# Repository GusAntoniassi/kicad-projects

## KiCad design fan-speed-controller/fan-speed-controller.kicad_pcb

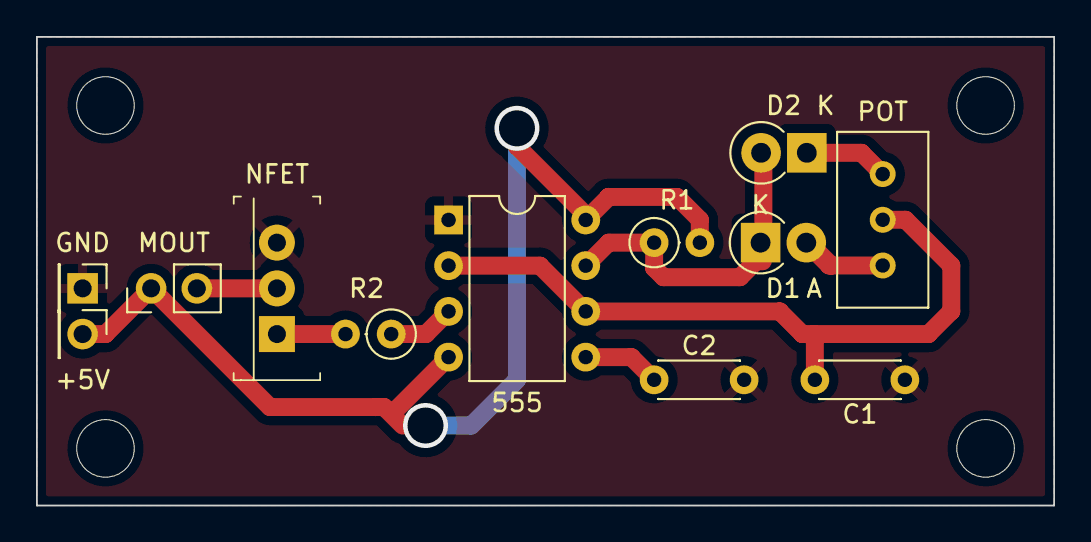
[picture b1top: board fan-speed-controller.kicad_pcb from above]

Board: 2 copper layers, 56.5 x 26.0 mm, 12 parts (0 on the bottom side), 10 nets.

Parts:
555: LM555xN; DIP-8_W7.62mm
+5V: MountingHole_Pad; PinHeader_1x01_P2.54mm_Vertical
C1: 100nF; C_Disc_D4.3mm_W1.9mm_P5.00mm
C2: 10nF; C_Disc_D4.3mm_W1.9mm_P5.00mm
D1: 1N4007; D_DO-41_SOD81_P2.54mm_Vertical_AnodeUp
D2: 1N4007; D_DO-41_SOD81_P2.54mm_Vertical_KathodeUp
GND: MountingHole_Pad; PinHeader_1x01_P2.54mm_Vertical
MOUT: Motor_DC; PinHeader_1x02_P2.54mm_Vertical
NFET: IRF510PBF; TO-220-3
POT: 1M; Potentiometer_Bourns_3386C_Horizontal
R1: 1K; R_Axial_DIN0207_L6.3mm_D2.5mm_P2.54mm_Vertical
R2: 440; R_Axial_DIN0207_L6.3mm_D2.5mm_P2.54mm_Vertical

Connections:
+5V: 555.4 (R), 555.8 (VCC), +5V.1, MOUT.1 (+), R1.2
GND: 555.1 (GND), C1.2, C2.2, GND.1, NFET.3 (S)
unnamed: 555.2 (TR), 555.6 (THR), C1.1, POT.2
unnamed: 555.5 (CV), C2.1
unnamed: 555.7 (DIS), D1.1 (K), D2.2 (A), R1.1
unnamed: D1.2 (A), POT.3
unnamed: D2.1 (K), POT.1
unnamed: MOUT.2 (-), NFET.2 (D)
unnamed: NFET.1 (G), R2.2
unnamed: 555.3 (Q), R2.1

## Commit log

2022-08-31 feat: add fan-speed-controller project
